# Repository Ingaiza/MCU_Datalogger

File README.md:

# MCU Datalogger Board

## Overview
This repository contains the KiCad PCB design files for a custom MCU Datalogger board. This board integrates robust non-volatile memory, real-time tracking capabilities, and essential communication interfaces. It serves as a reliable hardware foundation for capturing, storing, and transmitting sensor data in embedded systems.

## Hardware Features

* **Microcontroller**: Powered by the ATMEGA328P-AU 8-bit AVR microcontroller, running on a 16MHz external crystal.
* **Timekeeping**: Features an integrated DS1337S Real-Time Clock (RTC) equipped with a dedicated 32.768kHz crystal for precise timestamping of logged data.
* **Memory & Storage**: 
    * Dual 24LC1025 EEPROMs (U1 and U2) provide extensive, reliable onboard data storage over the I2C bus.
* **User Interface & Expansion**:
    * Dedicated headers for standard communication protocols: I2C and Serial UART.
    * Accessible GPIO breakout header for rapid prototyping and connecting external sensors.
    * Standard 6-pin ICSP header for direct programming and bootloader flashing.
    * Dual status LEDs (D1, D2) for easy visual debugging.

## Visuals & Documentation

### 3D Slanted View

### Board Layout & Routing

### Schematic
The complete circuit design can be viewed here: [Schematic PDF](media/schematic.pdf)

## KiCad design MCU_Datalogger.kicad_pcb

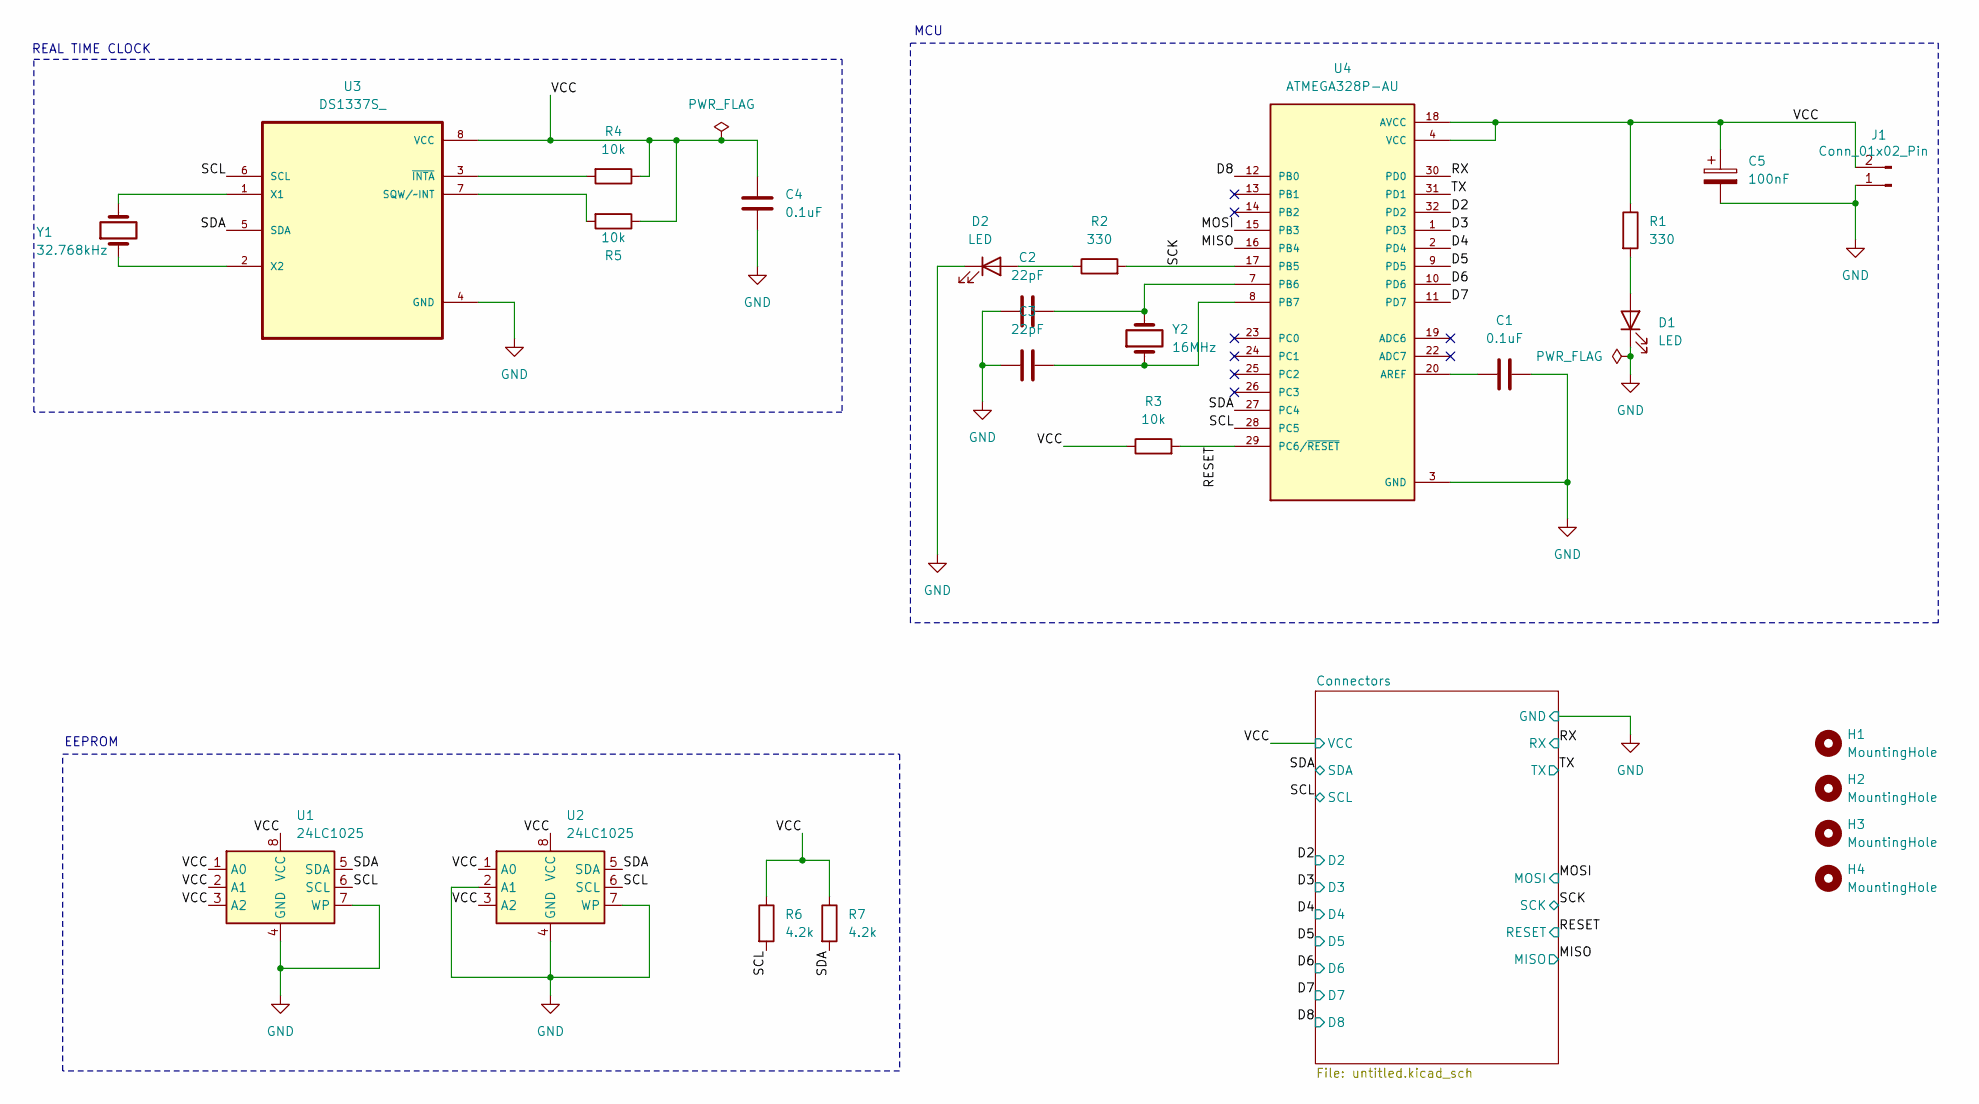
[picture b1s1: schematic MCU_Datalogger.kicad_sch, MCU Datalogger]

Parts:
C1, C4: 0.1uF; C_0805_2012Metric
C2, C3: 22pF; C_0805_2012Metric
C5: 100nF; C_0805_2012Metric
D1, D2: LED; LED_0805_2012Metric
H1, H2, H3, H4: MountingHole; MountingHole_2.1mm
J1: Conn_01x02_Pin; PinHeader_1x02_P2.54mm_Vertical
R1, R2: 330; R_0805_2012Metric
R3, R4, R5: 10k; R_0805_2012Metric
R6, R7: 4.2k; R_0805_2012Metric
U1, U2: 24LC1025; SOIC-8_5.3x5.3mm_P1.27mm
U3: DS1337S_; SOIC127P600X175-8N
U4: ATMEGA328P-AU; QFP80P900X900X120-32N; PARTREV 8271A
Y1: 32.768kHz; Crystal_SMD_5032-2Pin_5.0x3.2mm_HandSoldering
Y2: 16MHz; Crystal_SMD_5032-2Pin_5.0x3.2mm_HandSoldering

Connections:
/D2: U4.32 (PD2); also elsewhere on the board
/D3: U4.1 (PD3); also elsewhere on the board
/D4: U4.2 (PD4); also elsewhere on the board
/D5: U4.9 (PD5); also elsewhere on the board
/D6: U4.10 (PD6); also elsewhere on the board
/D7: U4.11 (PD7); also elsewhere on the board
/D8: U4.12 (PB0); also elsewhere on the board
/MISO: U4.16 (PB4); also elsewhere on the board
/MOSI: U4.15 (PB3); also elsewhere on the board
/RESET: R3.2, U4.29 (PC6/~RESET); also elsewhere on the board
/RX: U4.30 (PD0); also elsewhere on the board
/SCK: R2.2, U4.17 (PB5); also elsewhere on the board
/SCL: R6.2, U1.6 (SCL), U2.6 (SCL), U3.6 (SCL), U4.28 (PC5); also elsewhere on the board
/SDA: R7.2, U1.5 (SDA), U2.5 (SDA), U3.5 (SDA), U4.27 (PC4); also elsewhere on the board
/TX: U4.31 (PD1); also elsewhere on the board
GND: C1.1, C2.1, C3.1, C4.2, C5.2, D1.1 (K), D2.1 (K), J1.1, U1.4 (GND), U1.7 (WP), U2.2 (A1), U2.4 (GND), U2.7 (WP), U3.4 (GND), U4.3 (GND), U4.5 (GND), U4.21 (GND); also elsewhere on the board
unnamed: D1.2 (A), R1.2
unnamed: D2.2 (A), R2.1
unnamed: R5.2, U3.7 (SQW/~INT)
unnamed: U3.1 (X1), Y1.2
unnamed: U3.2 (X2), Y1.1
unnamed: R4.2, U3.3 (~INTA)
unnamed: C1.2, U4.20 (AREF)
unnamed: C2.2, U4.7 (PB6), Y2.2
unnamed: C3.2, U4.8 (PB7), Y2.1
VCC: C4.1, C5.1, J1.2, R1.1, R3.1, R4.1, R5.1, R6.1, R7.1, U1.1 (A0), U1.2 (A1), U1.3 (A2), U1.8 (VCC), U2.1 (A0), U2.3 (A2), U2.8 (VCC), U3.8 (VCC), U4.4 (VCC), U4.6 (VCC), U4.18 (AVCC); also elsewhere on the board

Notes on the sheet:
REAL TIME CLOCK
MCU
EEPROM

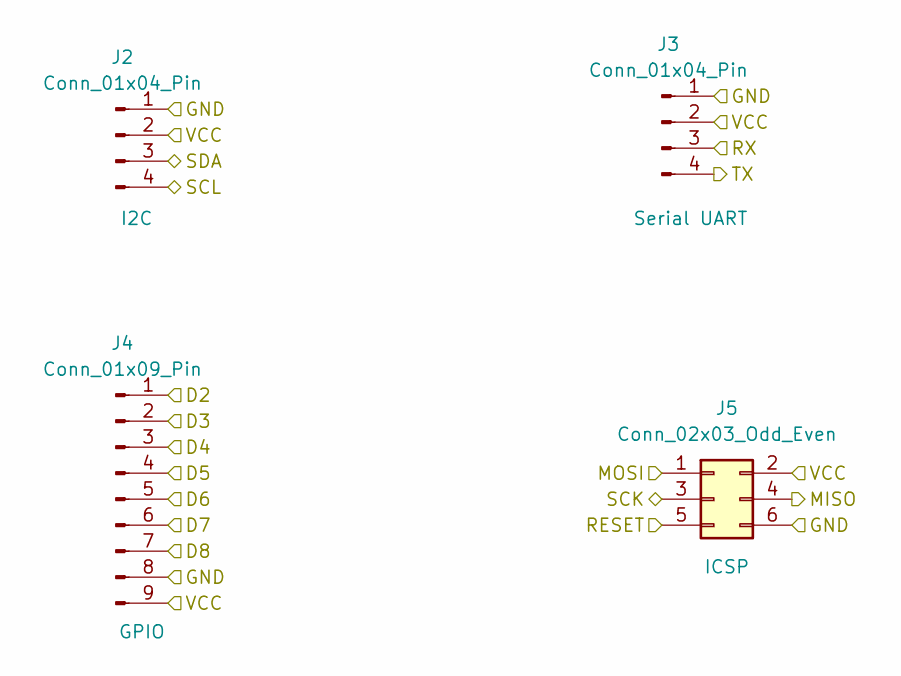
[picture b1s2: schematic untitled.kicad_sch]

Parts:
J2, J3: Conn_01x04_Pin; PinHeader_1x04_P2.54mm_Vertical
J4: Conn_01x09_Pin; PinHeader_1x09_P2.54mm_Vertical
J5: Conn_02x03_Odd_Even; PinHeader_2x03_P2.54mm_Vertical

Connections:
/D2: J4.1; also elsewhere on the board
/D3: J4.2; also elsewhere on the board
/D4: J4.3; also elsewhere on the board
/D5: J4.4; also elsewhere on the board
/D6: J4.5; also elsewhere on the board
/D7: J4.6; also elsewhere on the board
/D8: J4.7; also elsewhere on the board
/MISO: J5.4; also elsewhere on the board
/MOSI: J5.1; also elsewhere on the board
/RESET: J5.5; also elsewhere on the board
/RX: J3.3; also elsewhere on the board
/SCK: J5.3; also elsewhere on the board
/SCL: J2.4; also elsewhere on the board
/SDA: J2.3; also elsewhere on the board
/TX: J3.4; also elsewhere on the board
GND: J2.1, J3.1, J4.8, J5.6; also elsewhere on the board
VCC: J2.2, J3.2, J4.9, J5.2; also elsewhere on the board

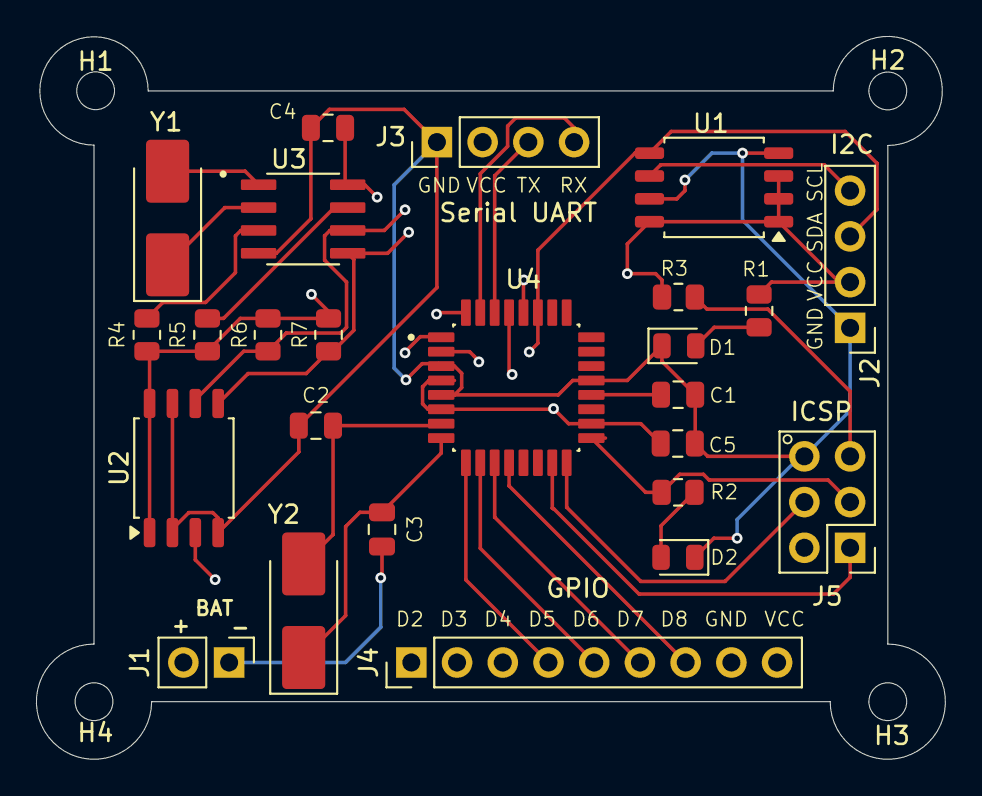
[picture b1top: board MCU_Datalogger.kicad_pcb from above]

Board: 4 copper layers, 50.5 x 40.2 mm, 29 parts (0 on the bottom side), 26 nets.

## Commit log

2026-02-13 Created Project folder
2026-02-14 Completed Schematic
2026-02-14 Completed PCB Setup and Design
2026-02-14 Fixed silkscreen text overlapp
2026-02-14 edited .gitignore
2026-02-16 Fixed RX TX misconnections
2026-02-16 Edited BAT footprint placement and silkscreen info
2026-02-16 4 Layer board setup
2026-02-16 board Edit
2026-02-16 Completed 4 Layer PCB Layout
2026-02-16 Edited Copper fills
2026-02-16 added media dir
2026-02-16 file update
2026-02-17 Fixed C4 Decoupling capacitor placement and added keep-out areas on Crystal Y1 & Y2 footprint areas
2026-03-13 Added README
2026-03-13 Fixed README
2026-03-13 zone fill to solid
